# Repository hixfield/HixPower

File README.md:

![Build with PlatformIO](https://img.shields.io/badge/build%20with-PlatformIO-orange?logo=data%3Aimage%2Fsvg%2Bxml%3Bbase64%2CPHN2ZyB3aWR0aD0iMjUwMCIgaGVpZ2h0PSIyNTAwIiB2aWV3Qm94PSIwIDAgMjU2IDI1NiIgeG1sbnM9Imh0dHA6Ly93d3cudzMub3JnLzIwMDAvc3ZnIiBwcmVzZXJ2ZUFzcGVjdFJhdGlvPSJ4TWlkWU1pZCI+PHBhdGggZD0iTTEyOCAwQzkzLjgxIDAgNjEuNjY2IDEzLjMxNCAzNy40OSAzNy40OSAxMy4zMTQgNjEuNjY2IDAgOTMuODEgMCAxMjhjMCAzNC4xOSAxMy4zMTQgNjYuMzM0IDM3LjQ5IDkwLjUxQzYxLjY2NiAyNDIuNjg2IDkzLjgxIDI1NiAxMjggMjU2YzM0LjE5IDAgNjYuMzM0LTEzLjMxNCA5MC41MS0zNy40OUMyNDIuNjg2IDE5NC4zMzQgMjU2IDE2Mi4xOSAyNTYgMTI4YzAtMzQuMTktMTMuMzE0LTY2LjMzNC0zNy40OS05MC41MUMxOTQuMzM0IDEzLjMxNCAxNjIuMTkgMCAxMjggMCIgZmlsbD0iI0ZGN0YwMCIvPjxwYXRoIGQ9Ik0yNDkuMzg2IDEyOGMwIDY3LjA0LTU0LjM0NyAxMjEuMzg2LTEyMS4zODYgMTIxLjM4NkM2MC45NiAyNDkuMzg2IDYuNjEzIDE5NS4wNCA2LjYxMyAxMjggNi42MTMgNjAuOTYgNjAuOTYgNi42MTQgMTI4IDYuNjE0YzY3LjA0IDAgMTIxLjM4NiA1NC4zNDYgMTIxLjM4NiAxMjEuMzg2IiBmaWxsPSIjRkZGIi8+PHBhdGggZD0iTTE2MC44NjkgNzQuMDYybDUuMTQ1LTE4LjUzN2M1LjI2NC0uNDcgOS4zOTItNC44ODYgOS4zOTItMTAuMjczIDAtNS43LTQuNjItMTAuMzItMTAuMzItMTAuMzJzLTEwLjMyIDQuNjItMTAuMzIgMTAuMzJjMCAzLjc1NSAyLjAxMyA3LjAzIDUuMDEgOC44MzdsLTUuMDUgMTguMTk1Yy0xNC40MzctMy42Ny0yNi42MjUtMy4zOS0yNi42MjUtMy4zOWwtMi4yNTggMS4wMXYxNDAuODcybDIuMjU4Ljc1M2MxMy42MTQgMCA3My4xNzctNDEuMTMzIDczLjMyMy04NS4yNyAwLTMxLjYyNC0yMS4wMjMtNDUuODI1LTQwLjU1NS01Mi4xOTd6TTE0Ni41MyAxNjQuOGMtMTEuNjE3LTE4LjU1Ny02LjcwNi02MS43NTEgMjMuNjQzLTY3LjkyNSA4LjMyLTEuMzMzIDE4LjUwOSA0LjEzNCAyMS41MSAxNi4yNzkgNy41ODIgMjUuNzY2LTM3LjAxNSA2MS44NDUtNDUuMTUzIDUxLjY0NnptMTguMjE2LTM5Ljc1MmE5LjM5OSA5LjM5OSAwIDAgMC05LjM5OSA5LjM5OSA5LjM5OSA5LjM5OSAwIDAgMCA5LjQgOS4zOTkgOS4zOTkgOS4zOTkgMCAwIDAgOS4zOTgtOS40IDkuMzk5IDkuMzk5IDAgMCAwLTkuMzk5LTkuMzk4em0yLjgxIDguNjcyYTIuMzc0IDIuMzc0IDAgMSAxIDAtNC43NDkgMi4zNzQgMi4zNzQgMCAwIDEgMCA0Ljc0OXoiIGZpbGw9IiNFNTcyMDAiLz48cGF0aCBkPSJNMTAxLjM3MSA3Mi43MDlsLTUuMDIzLTE4LjkwMWMyLjg3NC0xLjgzMiA0Ljc4Ni01LjA0IDQuNzg2LTguNzAxIDAtNS43LTQuNjItMTAuMzItMTAuMzItMTAuMzItNS42OTkgMC0xMC4zMTkgNC42Mi0xMC4zMTkgMTAuMzIgMCA1LjY4MiA0LjU5MiAxMC4yODkgMTAuMjY3IDEwLjMxN0w5NS44IDc0LjM3OGMtMTkuNjA5IDYuNTEtNDAuODg1IDIwLjc0Mi00MC44ODUgNTEuODguNDM2IDQ1LjAxIDU5LjU3MiA4NS4yNjcgNzMuMTg2IDg1LjI2N1Y2OC44OTJzLTEyLjI1Mi0uMDYyLTI2LjcyOSAzLjgxN3ptMTAuMzk1IDkyLjA5Yy04LjEzOCAxMC4yLTUyLjczNS0yNS44OC00NS4xNTQtNTEuNjQ1IDMuMDAyLTEyLjE0NSAxMy4xOS0xNy42MTIgMjEuNTExLTE2LjI4IDMwLjM1IDYuMTc1IDM1LjI2IDQ5LjM2OSAyMy42NDMgNjcuOTI2em0tMTguODItMzkuNDZhOS4zOTkgOS4zOTkgMCAwIDAtOS4zOTkgOS4zOTggOS4zOTkgOS4zOTkgMCAwIDAgOS40IDkuNCA5LjM5OSA5LjM5OSAwIDAgMCA5LjM5OC05LjQgOS4zOTkgOS4zOTkgMCAwIDAtOS4zOTktOS4zOTl6bS0yLjgxIDguNjcxYTIuMzc0IDIuMzc0IDAgMSAxIDAtNC43NDggMi4zNzQgMi4zNzQgMCAwIDEgMCA0Ljc0OHoiIGZpbGw9IiNGRjdGMDAiLz48L3N2Zz4=)

Hardware (schematic and PCB) and software for a WIFI connected intelligent power switch. It contains a temperature sensor, PIR motion sensor, button (with LED) and buzzer and is based on the ESP8266 microcontroller. Its measurements are pubished via MQTT and it can also be controlled via MQTT. Its part of my home automation system based on a raspberry pi running Mosquitoo, Nodered, InfluxDB and Grafana.

## Improvements

- [ ] Configuration of WIFI SSID/PWD via web interface
- [ ] 3D print design to keep DS18B20 neatly in bottom of the enclosure

## Brief overview

- WIFI connected
- MQTT firmware written using PlatformIO
- plugs directly into the wall socket
- intelligently switches loads upto 2000W on/off
- measures the room temperature
- detects movement (using PIR sensor)
- button on front pannel for manual operation
- led status indication on front panel
- based on popular [ESP8266](http://esp8266.com)

# Hardware
[Click here for hardware information](hardware/README.md)
# Software
[Click here for software information](software/README.md)
# overview

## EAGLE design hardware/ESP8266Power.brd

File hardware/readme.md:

# PCB
*(click for high resolution image)*

| Top                                              | Bottom                                                    |
|--------------------------------------------------|-----------------------------------------------------------|
|  |  |

# Components
## bill of materials
| Qty needed | Qty delivered | Part                                     | Value                    | Description                                                           | picture                                | 
|------------|---------------|------------------------------------------|--------------------------|-----------------------------------------------------------------------|----------------------------------------| 
| 2          | 3             | C1, C2                                   | 47uF                     | SMD, tantalum capacitor, 1206                                         | [picture](images/1206_cap_47uf.jpg)    | 
| 2          | 3             | C3, C4                                   | 100nF                    | SMD, capacitor, 1206                                                  | [picture](images/1206_cap_100nf.jpg)   | 
| 1          | 1             | C6                                       | 680uF / 4V               | Through hole, electrolytic capacitor, diameter 8mm, 3.5mm pin spacing | [picture](images/th_cap.jpg)          | 
| 10         | 11            | R1, R2, R3, R4, R5, R6, R7, R8, R10, R15 | 10K                      | SMD, resistor, 1206                                                   | [picture](images/1206_res_10k.jpg)     | 
| 1          | 2             | R9                                       | 4.7K                     | SMD, resistor, 1206                                                   | [picture](images/1206_res_4.7k.jpg)    | 
| 2          | 3             | R11, R12                                 | 330                      | SMD, resistor, 1206                                                   | [picture](images/1206_res_330.jpg)     | 
| 1          | 2             | R13                                      | 2.2K                     | SMD, resistor, 1206                                                   | [picture](images/1206_res_2.2k.jpg)    | 
| 1          | 1             | R14                                      | S10K275                  | Through hole, varistor                                                | [picture](images/th_s10k275.jpg)       | 
| 1          | 1             | F1                                       | 800mA                    | "Through hole, fuse, 8.35mm x 4 mm, 0.2"" (5.08mm) pin spacing "      | [picture](images/th_fuse_800ma.jpg)    | 
| 1          | 2             | LED1                                     | Red                      | SMD, led, 1206                                                        | [picture](images/1206_led_red.jpg)     | 
| 1          | 2             | D1                                       | BAV103                   | SMD, diode, SOD80                                                     | [picture](images/sod80_bav103.jpg)     | 
| 3          | 4             | T1, T2, T3                               | BC847C                   | SMD, NPN Transistor, SOT23                                            | [picture](images/sot23_bc847c.jpg)     | 
| 1          | 1             | B1                                       | 5V                       | "Through hole, buzzer, diameter 12mm, 0.3"" (7.62mm) pin spacing"     | [picture](images/th_buzzer.jpg)        | 
| 1          | 1             | U1                                       | ESP12E                   | SMD, ESP12E module                                                    | [picture](images/esp12e.jpg)           | 
| 1          | 1             | U2                                       | LM3940                   | SMD, Low drop voltage regulator, SOT223                               | [picture](images/sot223_lm3940.jpg)    | 
| 1          | 1             | U3                                       | HLK-PM01                 | Through hole, power module, HiLink HLK-PM01                           | [picture](images/th_hlk-pm01.jpg)      | 
| 1          | 1             | J1                                       | FTDI                     | "Through hole, header female,  6P,  0.1"" (2.54mm) pin spacing"       | [picture](images/th_ftdi.jpg)          | 
| 2          | 2             | S1, S2                                   | PROG, RST                | SMD Push button                                                       | [picture](images/micropushbutton.jpg)  | 
| 1          | 1             | S3                                       | SRD-05VDC-SL-C           | Through hole, Relay SRD-05VDC-SL-C                                    | [picture](images/relay.jpg)            | 
| 2          | 2             | PIR, SW                                  | XH3P                     | Through hole, Connector male XH3P straight                            | [picture](images/th_xh3pmale.jpg)      | 
| 1          | 1             | DS18B20 temp sensor encased              |                          | Module, DS18B20 temp sensor encased                                   | [picture](images/ds18b20.jpg)          | 
| 1          | 1             | PIR Module                               |                          | Module, PIR                                                           | [picture](images/pirmodule.jpg)        | 
| 1          | 1             | Switch with led                          |                          | Switch with led                                                       | [picture](images/pushbutton.jpg)       | 
| 2          | 2             | XH3P female no pins                      |                          | XH3P female no pins                                                   | [picture](images/xh3pfemalesolder.jpg) | 
| 2          | 2             | XH3P wire 10cm [pin -> solder], black    |                          | XH3P wire 10cm [pin -> solder], black                                 | [picture](images/xh3pfemalesolder.jpg) | 
| 1          | 1             | XH3P wire 10cm [pin -> solder], red      |                          | XH3P wire 10cm [pin -> solder], red                                   | [picture](images/xh3pfemalesolder.jpg) | 
| 1          | 1             | XH3P wire 10cm [pin -> solder], yellow   |                          | XH3P wire 10cm [pin -> solder], yellow                                | [picture](images/xh3pfemalesolder.jpg) | 
| 2          | 2             | XH3P wire 10cm [pin -> solder], white    |                          | XH3P wire 10cm [pin -> solder], white                                 | [picture](images/xh3pfemalesolder.jpg) | 
| 1          | 1             | Case                                     |                          | Case BOPLA 43432501, predrilled                                       | [picture](images/case.jpg)             | 
| 1          | 1             | PCB                                      |                          | Custom PCB                                                            | [picture](images/pcb.jpg)              | 
| 2          | 2             | Cable lug round M3                       |                          | Cable lug round M3                                                    | [picture](images/cablelugroundm3.jpg)  | 
| 1          | 1             | Cable lug fork M4                        |                          | Cable lug fork M4                                                     | [picture](images/cablelugforkm4.jpg)   | 
| 1          | 1             | Heat shrink tubing 1,5mm, 2.5mm, 6mm, 8mm|                          | Heat shrink tubing 1,5mm, 2.5mm, 6mm, 8mm                             | [picture](images/heatshrinktubing.jpg) | 
| 3          | 3             | PCB Fixation screw                       |                          | Allen screw, inox, M3 x 6mm thread length                             | [picture](images/screw.jpg)            | 
| 1          | 1             | 1.5mm2 x 55mm mains wire brown           |                          | 1.5mm2 x 55mm mains wire brown                                        | [picture](images/mainswire.jpg)        | 
| 1          | 1             | 1.5mm2 x 55mm mains wire blue            |                          | 1.5mm2 x 55mm mains wire blue                                         | [picture](images/mainswire.jpg)        | 
| 1          | 1             | 1.5mm2 x 55mm mains wire yellow/green    |                          | 1.5mm2 x 55mm mains wire yellow/green                                 | [picture](images/mainswire.jpg)        | 

## overview

# Assembly instructions
## soldering of the PCB
### Step 0: BC847 transistors

### Step 1: 10K resistors

### Step 2: 4.7K resistors

### Step 3: 330 resistors

### Step 4: 2.2K resistors

### Step 5: 100nF capacitors

### Step 6: 47uF tantalum capacitors

### Step 7: LM3940 voltage controller

### Step 8: LED

### Step 9: Diode

### Step 10: ESP12E

### Step 11: Push buttons

### Step 12: 680uF capacitor 

### Step 13: connectors

### Step 14: buzzer

### Step 15: relay

### Step 16: power supply

### Step 17: FTDI connector

### Step 18: Fuse

### Step 19: Varistor

## Assemble main wires
### Step 29: neutral (blue) and live (brown) mains connection wires

### Step 21: earthing wire (yellow/green)

## Assemble push button
### Step 22: prepare wires

### Step 23: connect (black) GND wire

### Step 24: connect (white) SWITCH wire

### Step 25: connect (yellow) + LED wire

### Step 26: shrink and put in housing

## Assemble PIR
### Step 27: prepare and connect wires

### Step 28: shrink and put in housing

### Step 29: adjust settings

- refer to [HC-SR501 Motion Sensor Tutorial]([http://henrysbench.capnfatz.com/henrys-bench/arduino-sensors-and-input/arduino-hc-sr501-motion-sensor-tutorial/#attachment%20wp-att-2111/0/]) http://henrysbench.capnfatz.com/henrys-bench/arduino-sensors-and-input/arduino-hc-sr501-motion-sensor-tutorial/#attachment%20wp-att-2111/0/
- trigger selection jumper => recommended REPEATABLE TRIGGER
- set correct sensitivy and delay setings (variable resistors)
 * Sensitivity Adjust => recommended MIDDLE
 * Time Delay Adjust  => recommended MINIMUM

## Prepare temperature sensor

##Build PCB in the case
- solder the temperature sensor to the pcb
 - red = 3.3v
 - black = GND
 - blue = DATA  
- put PCB in case and fix using the screws
- put the temp sensor through the hole in the case
- connect the mains and earth wires to the power pins in the case
- cut 10 mm of heat shrink tube 8mm and slide it over the temperature sensor to fix it

## Programming via the FTDI connector
If you want to program manually via the FTDI connector:

- DO NOT 	PLUG THE DEVICE IN THE POWER !
- put in your USB -> SERIAL connector
- Push the onboard buttons in the correct sequence:
 - push and keep pushing the PROG button
 - push the RESET (while keeping PROG pressed)
 - release both butons
- De device is now in programming mode 	

##Assemble front
- mount the push button in the front of the case
- fix / glue the PIR sensor in the front of the case

##Assemble the device
- assemble front and back of case
 - connect push button connector
 - connect PIR connector
- close case and put in the screws  

# Packaging
- 330 gr (including box)
- ideal box would be approx 70mm x 130mm x 100 mm
# Case preparation

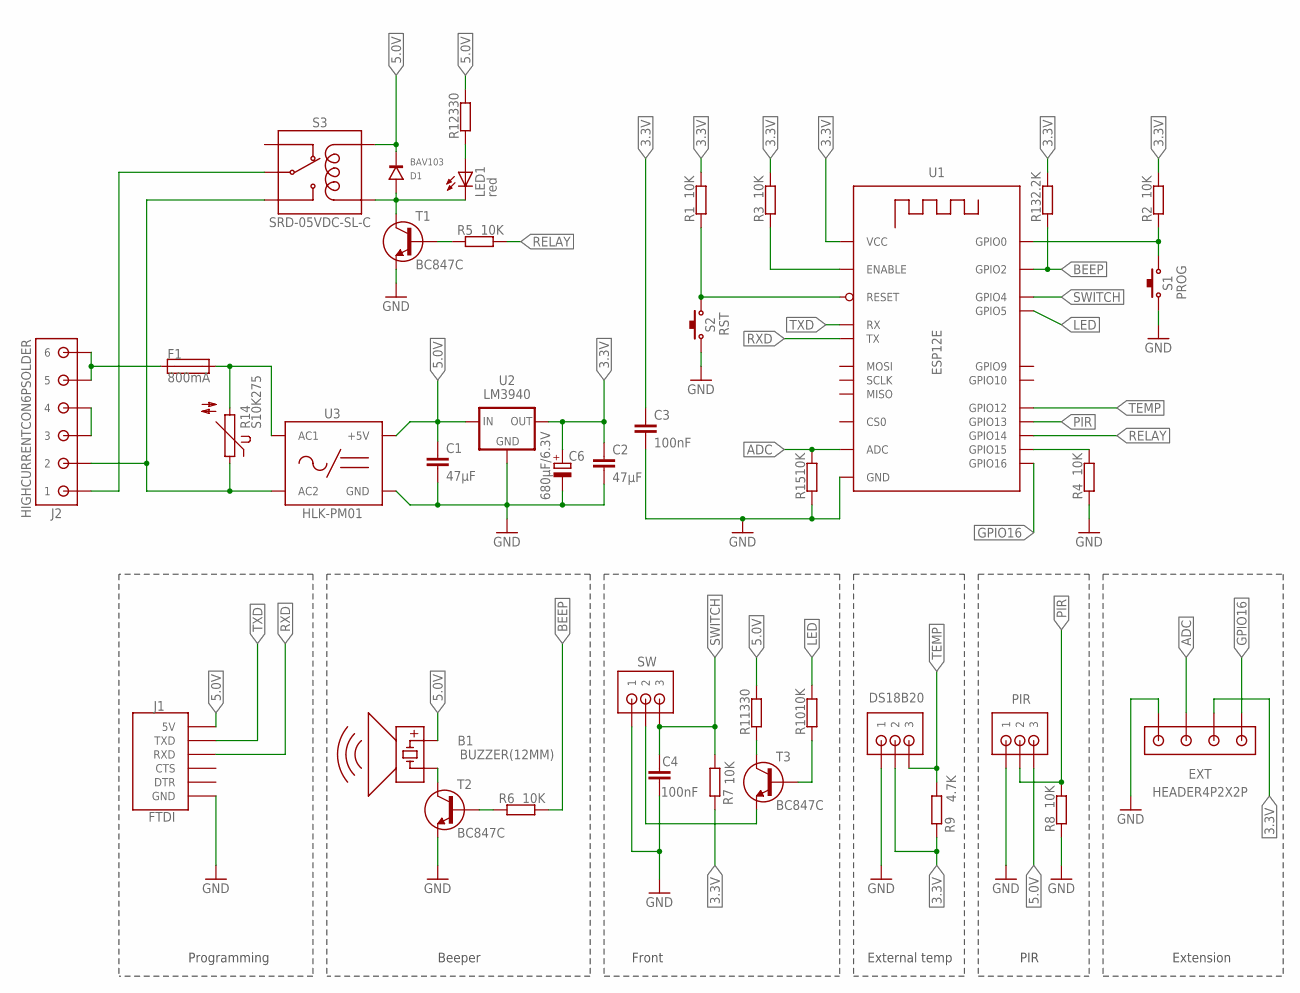
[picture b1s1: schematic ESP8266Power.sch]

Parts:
B1: BUZZER(12MM)
C1, C2: 47μF; C1206
C3, C4: 100nF; C1206
C6: 680μF/6.3V; E3,5-8
D1: BAV103; SOD80_DO213AA_MINIMELF
DS18B20: XH3P
EXT: HEADER4P2X2P; HEADER2X2P
F1: 800mA; FUSE_508
J1: FTDI
J2: HIGHCURRENTCON6PSOLDER; HIGHCURRENTCON6P_SOLDER
LED1: red; CHIPLED_1206
PIR: XH3P
R1, R2, R3, R4, R5, R6, R7, R8, R10, R15: 10K; R1206
R9: 4.7K; R1206
R11, R12: 330; R1206
R13: 2.2K; R1206
R14: S10K275
S1: PROG; SMDPUSHBTN_TYPE1
S2: RST; SMDPUSHBTN_TYPE1
S3: SRD-05VDC-SL-C
SW: XH3P
T1, T2, T3: BC847C; SOT23
U1: ESP12E; ESP8266(ESP12E)
U2: LM3940; SOT223
U3: HLK-PM01

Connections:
3.3V: C2.1, C3.1, C6.+, DS18B20.2, EXT.2, R1.2, R2.2, R3.2, R7.2, R9.2, R13.2, U1.VCC, U2.3 (OUT)
5.0V: B1.+, C1.1, D1.C, J1.5V, PIR.3, R11.2, R12.2, S3.COIL1, U2.1 (IN), U3.VO+ (+5V)
AC1: F1.2, R14.2, U3.AC1
AC2: J2.2, R14.1, S3.SW-NORMAL_OPEN, U3.AC2
ADC: EXT.3, R15.2, U1.ADC
BEEP: R6.2, R13.1, U1.GPIO2
EARTH: J2.3, J2.4
ENABLE: R3.1, U1.CH_PD (ENABLE)
GND: C1.2, C2.2, C3.2, C4.2, C6.-, DS18B20.1, EXT.4, J1.GND, PIR.1, R4.1, R8.1, R15.1, S1.2, S2.2, SW.1, T1.2 (E), T2.2 (E), U1.GND, U2.2 (GND), U2.4 (GND), U3.VO- (GND)
GPIO0: R2.1, S1.1, U1.GPIO0
GPIO15: R4.2, U1.GPIO15
GPIO16: EXT.1, U1.GPIO16
LED: R10.2, U1.GPIO5
LOAD: J2.1, S3.SW-COMMON
unnamed: R5.1, T1.1 (B)
unnamed: D1.A, LED1.C, S3.COIL0, T1.3 (C)
unnamed: R6.1, T2.1 (B)
unnamed: B1.-, T2.3 (C)
unnamed: R10.1, T3.1 (B)
unnamed: R11.1, T3.3 (C)
unnamed: SW.2, T3.2 (E)
unnamed: LED1.A, R12.1
unnamed: F1.1, J2.5, J2.6
PIR: PIR.2, R8.2, U1.GPIO13
RELAY: R5.2, U1.GPIO14
RESET: R1.1, S2.1, U1.RESET
RXD: J1.RXD, U1.TXD0 (TX)
SWITCH: C4.1, R7.1, SW.3, U1.GPIO4
TEMP: DS18B20.3, R9.1, U1.GPIO12
TXD: J1.TXD, U1.RXD0 (RX)

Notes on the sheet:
Front
Beeper
Programming
External temp
PIR
Extension

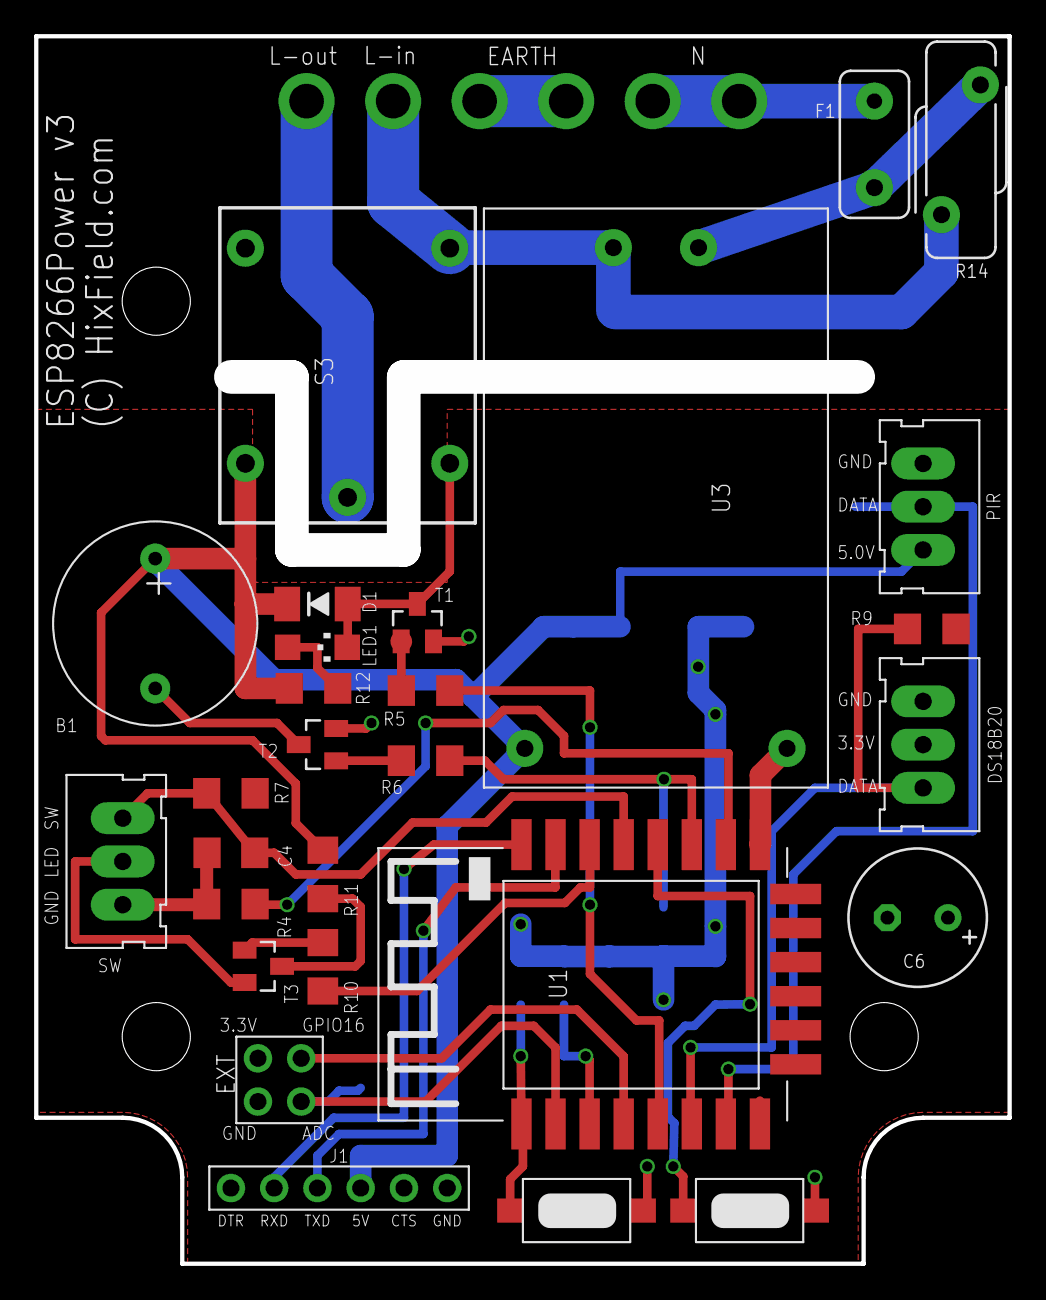
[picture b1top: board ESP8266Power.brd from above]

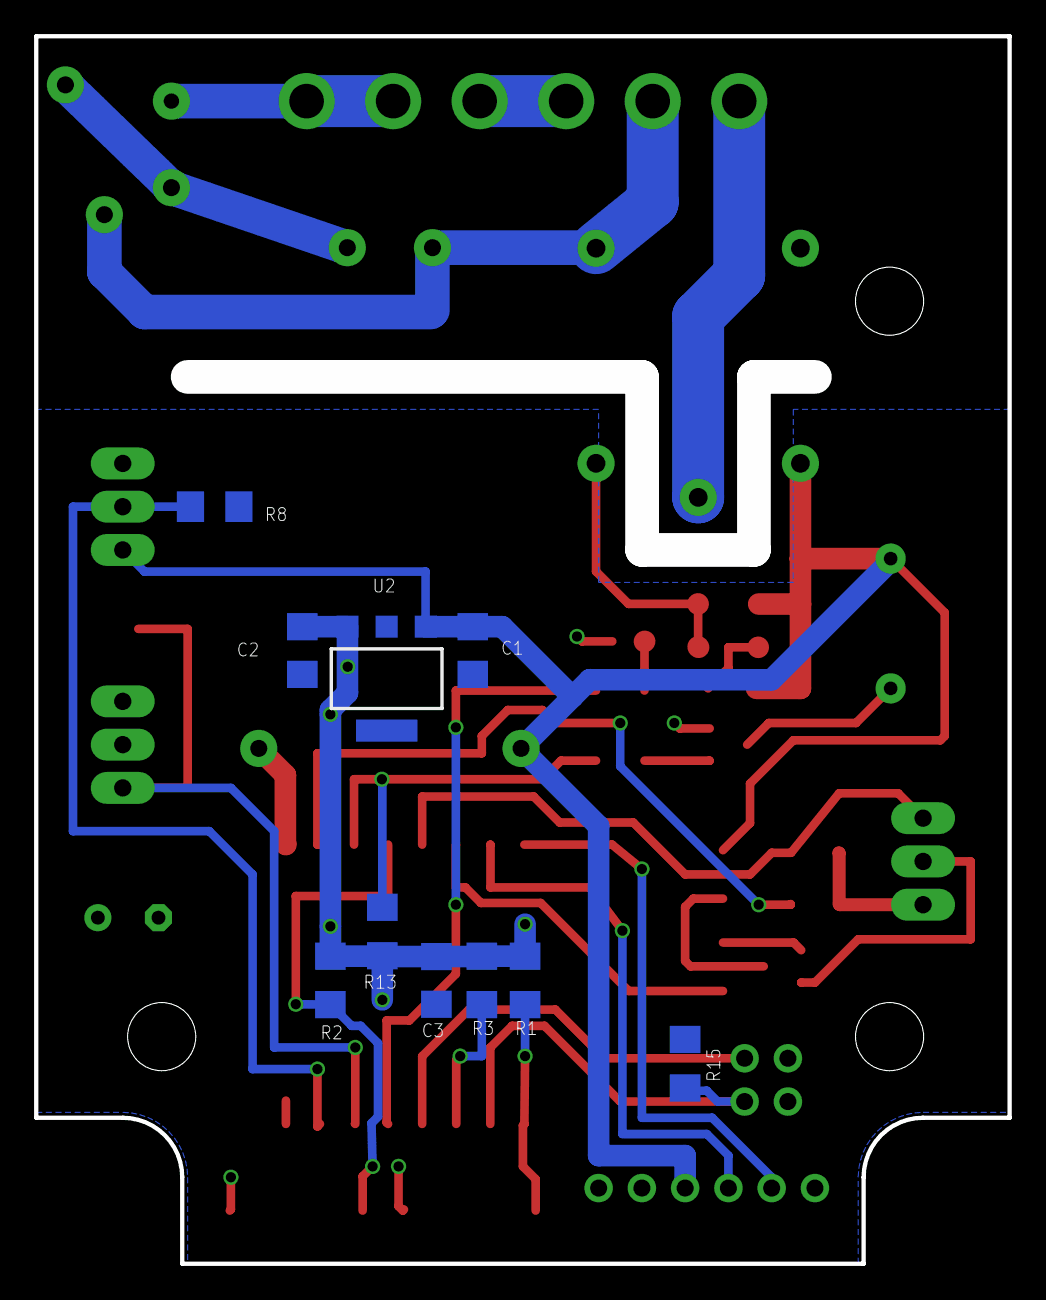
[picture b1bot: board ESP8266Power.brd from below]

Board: 2 copper layers, 57.1 x 72.1 mm, 39 parts (10 on the bottom side), 30 nets.

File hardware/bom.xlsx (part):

price excl | subtotal | Qty needed | Qty delivered | Part | Value | Description | picture | picture | Manufacturer | Manufacturer description | link | Device (Eagle) | Package | Description
0.1 | 0.2 | 2 | 3 | C1, C2 | 47uF | SMD, tantalum capacitor, 1206 | [picture](images/1206_cap_47uf.jpg) | 1206_cap_47uf.jpg | aliexpress | 47uF 6.3V 1206 SMD Tantalum Capacitor +/-20% A Type | https://www.aliexpress.com/item/47uF-6-3V-1206-SMD-Tantalum-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 | C-EUC1206 | C1206 | CAPACITOR, European symbol
8.5500000000000003E-3 | 1.7100000000000001E-2 | 2 | 3 | C3, C4 | 100nF | SMD, capacitor, 1206 | [picture](images/1206_cap_100nf.jpg) | 1206_cap_100nf.jpg | aliexpress | Free shipping 1206 SMD capacitor 100nf 50V 104Z 200pcs | https://www.aliexpress.com/item/Free-shipping-1206-SMD-capac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 | C-EUC1206 | C1206 | CAPACITOR, European symbol
5.5999999999999994E-2 | 5.5999999999999994E-2 | 1 | 1 | C6 | 680uF / 4V | Through hole, electrolytic capacitor, diameter 8mm, 3.5mm pin spacing | [picture](images/th_cap_470uf.jpg) | th_cap_470uf.jpg | aliexpress | Free shipping 100PCS 4V 680UF Aluminum electrolytic capacitors 680uF 4V 8*8mm G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 | https://www.aliexpress.com/item/Free-shipping-100PCS-4V-680U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 | CPOL-EUE3.5-8 | E3,5-8 | POLARIZED CAPACITOR, European symbol
3.7599999999999999E-3 | 3.7600000000000001E-2 | 10 | 11 | R1, R2, R3, R4, R5, R6, R7, R8, R10, R15 | 10K | SMD, resistor, 1206 | [picture](images/1206_res_10k.jpg) | 1206_res_10k.jpg | aliexpress | 500pcs 1206 SMD Resistor 1% 10K ohm | https://www.aliexpress.com/store/product/1206-SMD-Resistor-5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 | R-EU_R1206 | R1206 | RESISTOR, European symbol
3.7599999999999999E-3 | 3.7599999999999999E-3 | 1 | 2 | R9 | 4.7K | SMD, resistor, 1206 | [picture](images/1206_res_4.7k.jpg) | 1206_res_4.7k.jpg | aliexpress | 500pcs 1206 SMD Resistor 1% 4.7 ohm | https://www.aliexpress.com/store/product/1206-SMD-Resistor-5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 | R-EU_R1206 | R1206 | RESISTOR, European symbol
3.7599999999999999E-3 | 7.5199999999999998E-3 | 2 | 3 | R11, R12 | 330 | SMD, resistor, 1206 | [picture](images/1206_res_330.jpg) | 1206_res_330.jpg | aliexpress | 500pcs 1206 SMD Resistor 1% 330 ohm | https://www.aliexpress.com/item/1206-SMD-Resistor-5-330-ohm-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 | R-EU_R1206 | R1206 | RESISTOR, European symbol
3.7599999999999999E-3 | 3.7599999999999999E-3 | 1 | 2 | R13 | 2.2K | SMD, resistor, 1206 | [picture](images/1206_res_2.2k.jpg) | 1206_res_2.2k.jpg | aliexpress | 500pcs 1206 SMD Resistor 1% 2.2K ohm | https://www.aliexpress.com/store/product/1206-SMD-Resistor-5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 | R-EU_R1206 | R1206 | RESISTOR, European symbol
0.28000000000000003 | 0.28000000000000003 | 1 | 1 | R14 | S10K275 | Through hole, varistor | [picture](images/th_s10k275.jpg) | th_s10k275.jpg | conrad | Schijfvaristor S10K275 430 V Epcos S10K275 1 stuks | http://www.conrad.be/ce/nl/product/500592/Schijfvaristor-S10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 | S10K275 | S10K275 | VARISTOR
0.27 | 0.27 | 1 | 1 | F1 | 800mA | Through hole, fuse, 8.35mm x 4 mm, 0.2" (5.08mm) pin spacing | [picture](images/th_fuse_800ma.jpg) | th_fuse_800ma.jpg | conrad | ESKA 883116 Printzekering Radiaal bedraad Hoekig 800 mA 250 V Traag -T- 1 stuks | http://www.conrad.be/ce/nl/product/537512/ESKA-883116-Printz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 | FUSE | FUSE_508 | FUSE
0.01 | 0.01 | 1 | 2 | LED1 | Red | SMD, led, 1206 | [picture](images/1206_led_red.jpg) | 1206_led_red.jpg | aliexpress | 100PCS/LOT 1206 Red SMD LED Diode Light 3216 Diodes SMD Super Bright 1206 led 3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 | https://www.aliexpress.com/item/100PCS-LOT-1206-Red-SMD-LED-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 | CHIPLED_1206 | CHIPLED_1206 | LED
2.0999999999999998E-2 | 2.0999999999999998E-2 | 1 | 2 | D1 | BAV103 | SMD, diode, SOD80 | [picture](images/sod80_bav103.jpg) | sod80_bav103.jpg | gotron | SMD Si-diode 250V 200mA per 10st | https://www.gotron.be/signal-diode-smd-si-diode-250v-200ma-m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 | BAV100-101-102-103 | SOD80_DO213AA_MINIMELF
2.5000000000000001E-2 | 7.5000000000000011E-2 | 3 | 4 | T1, T2, T3 | BC847C | SMD, NPN Transistor, SOT23 | [picture](images/sot23_bc847c.jpg) | sot23_bc847c.jpg | gotron | BC847C transistor SMD NPN 45V 0,5A 0,25W B:420-800 SOT23 (per 10st) | https://www.gotron.be/bc847c-transistor-smd-npn-45v-0-5a-0-2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 | BC847 | SOT23 | 45 V, 100 mA NPN general-purpose transistors
0.09 | 0.09 | 1 | 1 | B1 | 5V | Through hole, buzzer, diameter 12mm, 0.3" (7.62mm) pin spacing | [picture](images/th_buzzer.jpg) | th_buzzer.jpg | conrad | 5V active buzzer 5V buzzer diameter 12MM* high 9.5MM long sound split 12095--DY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 | https://www.aliexpress.com/item/5V-active-buzzer-5V-buzzer-d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 | Buzzer | Diameter 12mm, 0.3" (7.62mm) pin spacing
1.8 | 1.8 | 1 | 1 | U1 | ESP12E | SMD, ESP12E module | [picture](images/esp12e.jpg) | esp12e.jpg | aliexpress | 2015 New version 1PCS ESP-12F (ESP-12E upgrade) ESP8266 remote serial Port WIFI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 | https://www.aliexpress.com/item/2015-New-version-1PCS-ESP-12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 | ESP8266(ESP12E)SMD | ESP8266(ESP12E) | ESP12E Module
0.71 | 0.71 | 1 | 1 | U2 | LM3940 | SMD, Low drop voltage regulator, SOT223 | [picture](images/sot223_lm3940.jpg) | sot223_lm3940.jpg | aliexpress | 20pcs LM3940IMPX-3.3 LM3940IMPX LM3940 L52B Manu: NS Encapsulation: SOT-223 | https://www.aliexpress.com/item/20pcs-LM3940IMPX-3-3-LM3940I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 | LM3940 | SOT223
2.34 | 2.34 | 1 | 1 | U3 | HLK-PM01 | Through hole, power module, HiLink HLK-PM01 | [picture](images/th_hlk-pm01.jpg) | th_hlk-pm01.jpg | aliexpress | 10 pcs HLK-PM01 AC-DC 220V to 5V Step-Down Buck Power Supply Module Intelligent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 | https://www.aliexpress.com/item/HLK-PM01-AC-DC-220V-to-5V-St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 | HLK-PM01 | HLK-PM01
0.1105 | 0.1105 | 1 | 1 | J1 | FTDI | Through hole, header female, 6P, 0.1" (2.54mm) pin spacing | [picture](images/th_ftdi.jpg) | th_ftdi.jpg | aliexpress | 20Pcs/lot High Quality 1*6P 2.54mm Pitch 6 Pin Female Single Row Straight Heade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 | https://www.aliexpress.com/item/20Pcs-lot-freeshipping-1-6P-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 | FTDI | FTDI
3.6000000000000004E-2 | 7.2000000000000008E-2 | 2 | 2 | S1, S2 | PROG, RST | SMD Push button | [picture](images/micropushbutton.jpg) | micropushbutton.jpg | aliexpress | 100PCS 3*6*2.5 mm 3*6*2.5 mm 3*6*2.5H SMD White Button switch key switch Tact S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 | https://www.aliexpress.com/item/100PCS-3-6-2-5-mm-3-6-2-5-mm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 | PUSHBTN | SMDPUSHBTN_TYPE1
0.33999999999999997 | 0.33999999999999997 | 1 | 1 | S3 | SRD-05VDC-SL-C | Through hole, Relay SRD-05VDC-SL-C | [picture](images/relay.jpg) | relay.jpg | aliexpress | 10PCS RELAY 5V SRD-5VDC-SL-C T73-5V Power Relay NEW GOOD QUALITY | https://www.aliexpress.com/item/10PCS-RELAY-5V-SRD-5VDC-SL-C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 | SRD-05VDC-SL-CPTH | SRD-05VDC-SL-C | SONGLE RELAY SRD-05VDC-SL-C
1.4039999999999999E-2 | 2.8079999999999997E-2 | 2 | 2 | PIR, SW | XH3P | Through hole, Connector male XH3P straight | [picture](images/th_xh3pmale.jpg) | th_xh3pmale.jpg | aliexpress | XH2.54mm connector straight pin XH-2P/3P/4P/5P/6P/7P/8P/9P/10P/11P/12P Socket T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 | https://www.aliexpress.com/item/XH2-54mm-connector-straight-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 | XH3P | XH3P
1.536 | 1.536 | 1 | 1 | DS18B20 temp sensor encased |  | Module, DS18B20 temp sensor encased | [picture](images/ds18b20.jpg) | ds18b20.jpg | aliexpress | J34 10 pcs/lot Wholesale&Retail High Quality Waterproof Digital Temperature Tem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 | https://www.aliexpress.com/item/J34-10-pcs-lot-Wholesale-Ret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
0.998 | 0.998 | 1 | 1 | PIR Module |  | Module, PIR | [picture](images/pirmodule.jpg) | pirmodule.jpg | aliexpress | 86076 Free Shipping 5pcs SR501 HC-SR501 Adjust IR Pyroelectric Infrared PIR mod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 | https://www.aliexpress.com/item/15925-Free-Shipping-SR501-HC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
2.081 | 2.081 | 1 | 1 | Switch with led |  | Switch with led | [picture](images/pushbutton.jpg) | pushbutton.jpg | aliexpress | 1202 Domed plastic momentary dot light Pin terminal illuminated pushbutton swit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 | https://www.aliexpress.com/item/1202-Domed-plastic-momentary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
0.05 | 0.1 | 2 | 2 | XH3P female no pins |  | XH3P female no pins | [picture](images/xh3pfemalesolder.jpg) | xh3pfemalesolder.jpg | aliexpress
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
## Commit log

2017-04-23 hardware v3
2017-04-23 corrected typo in hardware readme
2017-04-23 updated main readme
2017-04-23 corrected capitals
2017-04-23 added standalone software
2017-04-24 added remote debug source files
2017-05-07 added pcb assembly instructions
2017-05-08 added mains wires assembly instructions
2017-05-08 update headings
2017-05-13 added instructions for push button
2017-05-13 correct some faulty numbering
2017-05-13 corrected some typos
2017-05-13 corrected BOM
2017-05-13 corrected some numbering of the steps
2017-05-14 added per instructions
2017-05-14 updated naming of some images
2017-05-14 updated link
2017-05-14 added instructions for temp sensor and total assembling
2017-05-14 added buy button
2017-05-14 updated buy button
2017-05-14 added correct link to eBay
2017-05-21 added IBM BlueMix support
2017-05-21 update gitignore
2017-05-21 update git ignore
2017-05-21 updated software bluemix readme
2017-05-21 moved software images in readme
2017-06-13 updated pcb images
2017-06-13 corrected numbering errors for the resistors in the assembling instructions
2019-12-15 first mqtt version
2019-12-15 moved WIFI and MQTT settings to secret.h that is no checked in to public github repo
2020-01-04 start updating new firmware
2020-01-04 readme rename
2020-01-04 updated firmware for MQTT
2020-01-04 added secret.h
2020-01-04 update secret.h and data
2020-01-04 fixed bug publishing influxDB data (max mqtt package size was to small)
2020-01-11 reported motion now stays true while detected (not only at rising edge)
2020-01-11 added power cable dimensions
2020-01-18 updated readme + fix OTA
2020-02-10 fix issue saving to eeprom
2020-04-03 fix to update timeout immediatly when recieved via MQTT (and not after reboot)
2020-11-29 update upload settings
2020-11-29 just pinks the relay (and led) for testint
2020-11-30 add input interupt begin
2020-12-27 publishing wifi_rssi and wifi_mac in influxdb topic
2020-12-29 added build timestamp to mqtt and config interface
2021-01-01 test new HixArduino lib
2022-01-01 switched DS18B20 to arduino lib
2022-01-01 removed unusaged files
2022-01-01 changing heat timeout now always shutsoff the heating as well
